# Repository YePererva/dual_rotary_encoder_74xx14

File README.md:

# Module 2 with incremental rotary encoders and hardware bebouncing

 Paired Rotaty Encoder module with debouncing circuitry

## Layout and dimentions

| Top View	| Bottom View |
| ----- | ----- |
|  |  |

- overall dimensions: 1.0 in × 2.5 in
- mounting holes spacing : 0.75 in × 2.25 in
- mounting holes size : M3
- SMD sized:
	- Resistors: 0805
	- Capacitors : 0805
	- Diodes : MiniMELF

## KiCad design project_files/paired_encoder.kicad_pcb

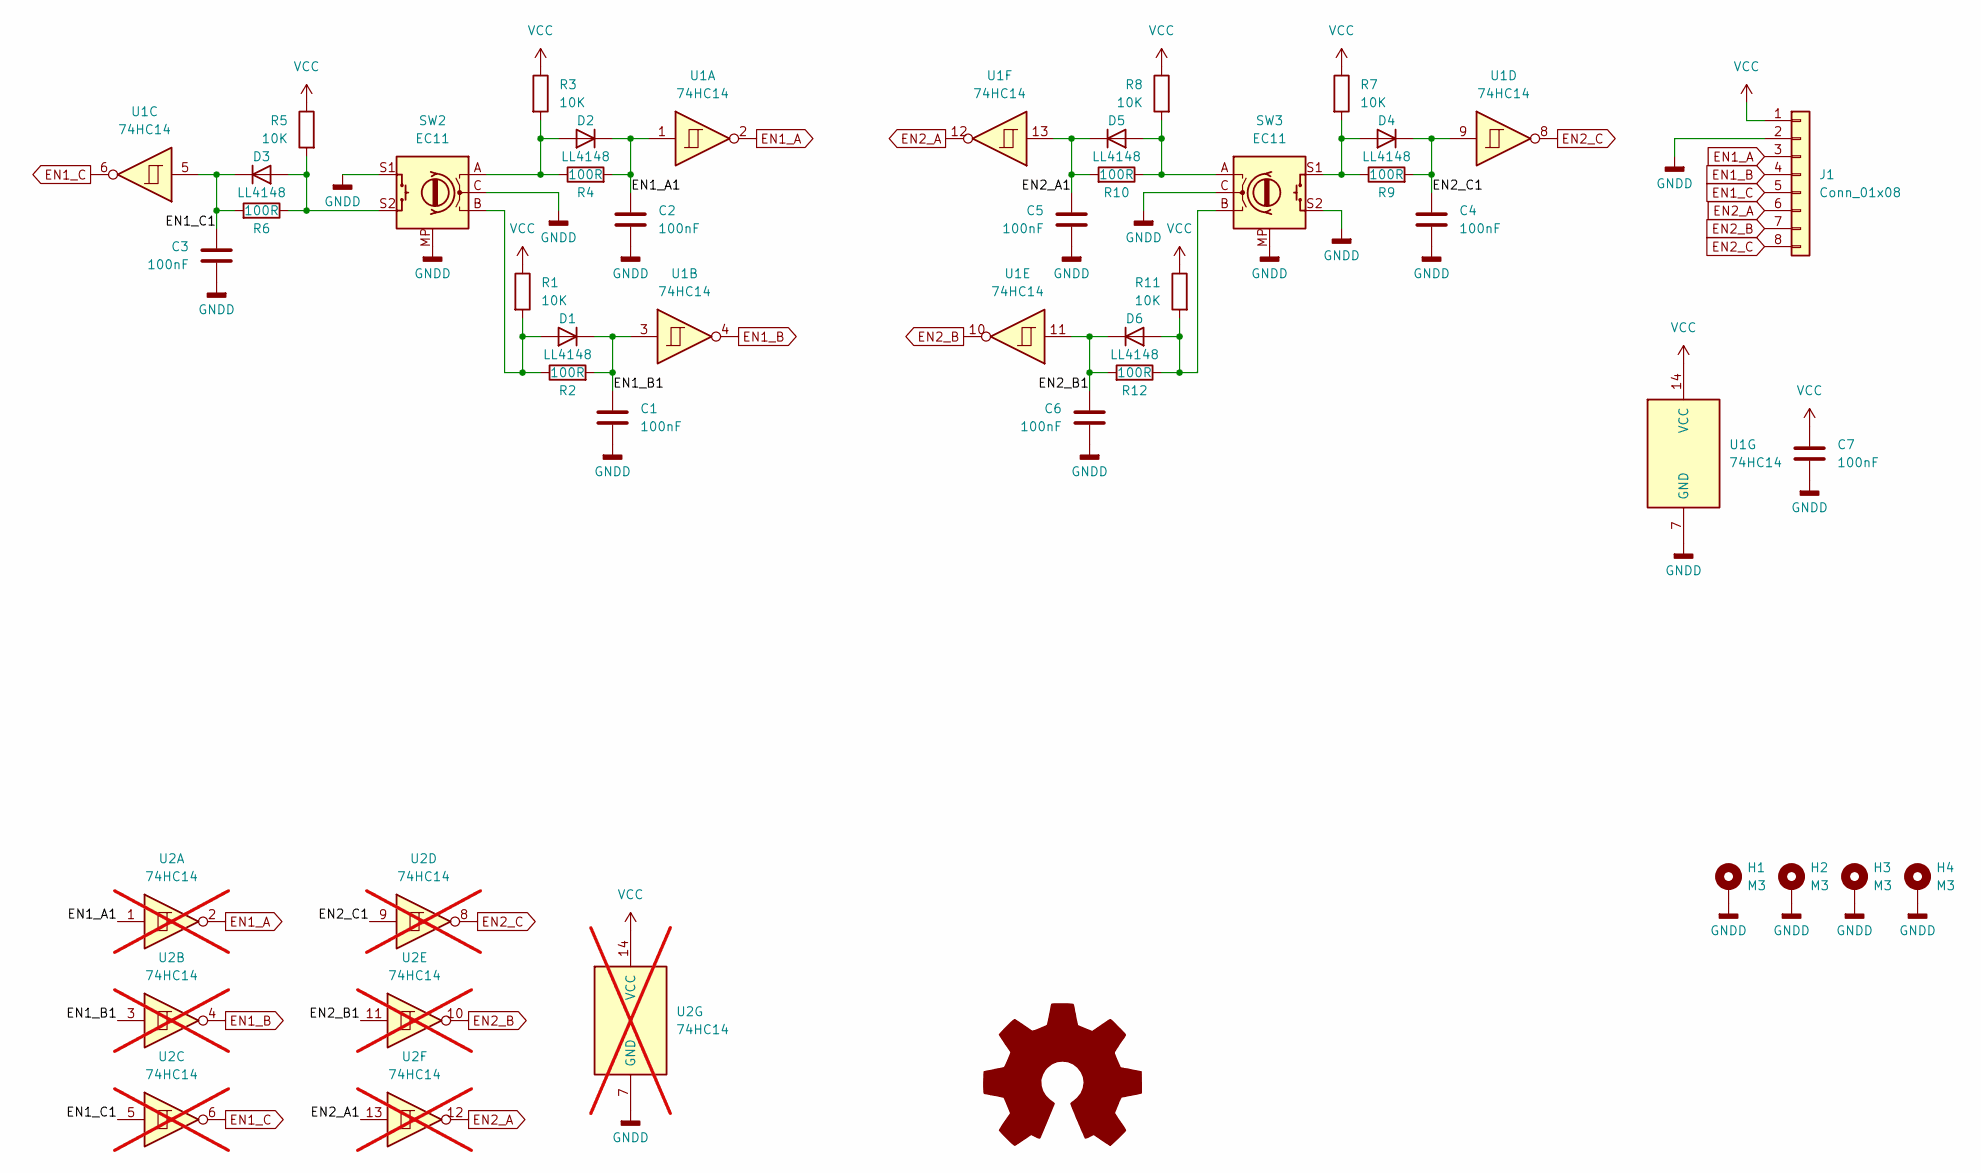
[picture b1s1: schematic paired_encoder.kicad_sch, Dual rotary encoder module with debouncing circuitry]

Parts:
C1, C2, C3, C4, C5, C6, C7: 100nF; C_0805_2012Metric
D1, D2, D3, D4, D5, D6: LL4148; D_MiniMELF
H1, H2, H3, H4: M3; MountingHole_2.7mm_Pad_Via
J1: Conn_01x08; PinHeader_1x08_P2.54mm_Vertical
R1, R3, R5, R7, R8, R11: 10K; R_0805_2012Metric
R2, R4, R6, R9, R10, R12: 100R; R_0805_2012Metric
SW2, SW3: EC11; RotaryEncoder_Alps_EC11E-Switch_Vertical_H20mm
U1: 74HC14; DIP-14_W7.62mm
U2: 74HC14; SOIC-14_3.9x8.7mm_P1.27mm; not fitted

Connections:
/EN1_A1: C2.1, D2.1 (K), R4.2, U1.1, U2.1
/EN1_B1: C1.1, D1.1 (K), R2.2, U1.3, U2.3
/EN1_C1: C3.1, D3.1 (K), R6.2, U1.5, U2.5
/EN2_A1: C5.1, D5.1 (K), R10.2, U1.13, U2.13
/EN2_B1: C6.1, D6.1 (K), R12.2, U1.11, U2.11
/EN2_C1: C4.1, D4.1 (K), R9.2, U1.9, U2.9
EN1_A: J1.3, U1.2, U2.2
EN1_B: J1.4, U1.4, U2.4
EN1_C: J1.5, U1.6, U2.6
EN2_A: J1.6, U1.12, U2.12
EN2_B: J1.7, U1.10, U2.10
EN2_C: J1.8, U1.8, U2.8
GNDD: C1.2, C2.2, C3.2, C4.2, C5.2, C6.2, C7.2, H1.1, H2.1, H3.1, H4.1, J1.2, SW2.C, SW2.MP, SW2.S1, SW3.C, SW3.MP, SW3.S2, U1.7 (GND), U2.7 (GND)
unnamed: D1.2 (A), R1.2, R2.1, SW2.B
unnamed: D2.2 (A), R3.2, R4.1, SW2.A
unnamed: D3.2 (A), R5.2, R6.1, SW2.S2
unnamed: D4.2 (A), R7.2, R9.1, SW3.S1
unnamed: D5.2 (A), R8.2, R10.1, SW3.A
unnamed: D6.2 (A), R11.2, R12.1, SW3.B
VCC: C7.1, J1.1, R1.1, R3.1, R5.1, R7.1, R8.1, R11.1, U1.14 (VCC), U2.14 (VCC)

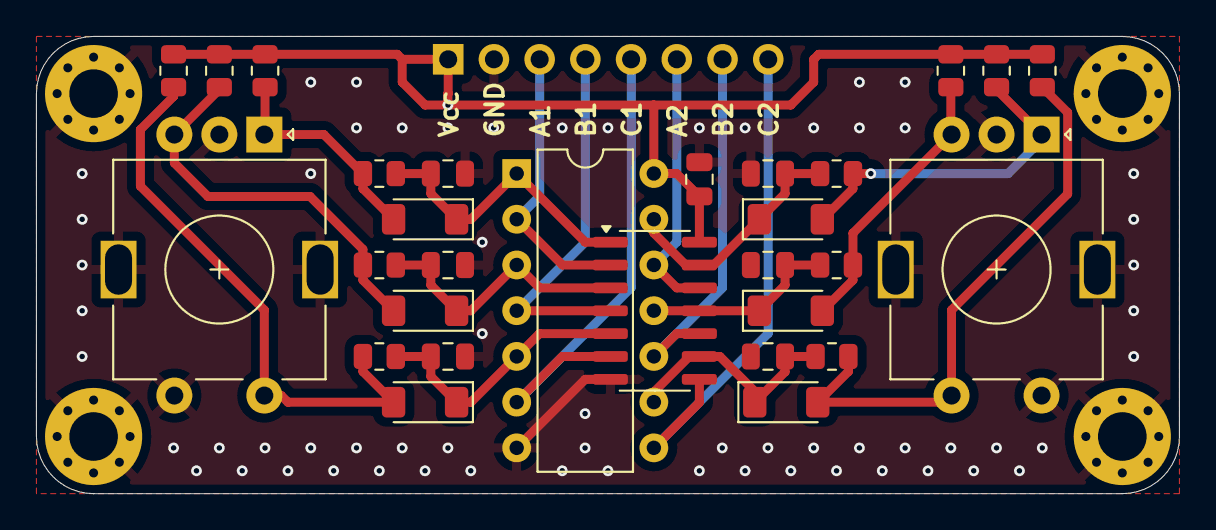
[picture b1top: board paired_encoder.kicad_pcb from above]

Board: 2 copper layers, 63.5 x 25.4 mm, 34 parts (1 on the bottom side), 20 nets.

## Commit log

2024-06-01 Start
